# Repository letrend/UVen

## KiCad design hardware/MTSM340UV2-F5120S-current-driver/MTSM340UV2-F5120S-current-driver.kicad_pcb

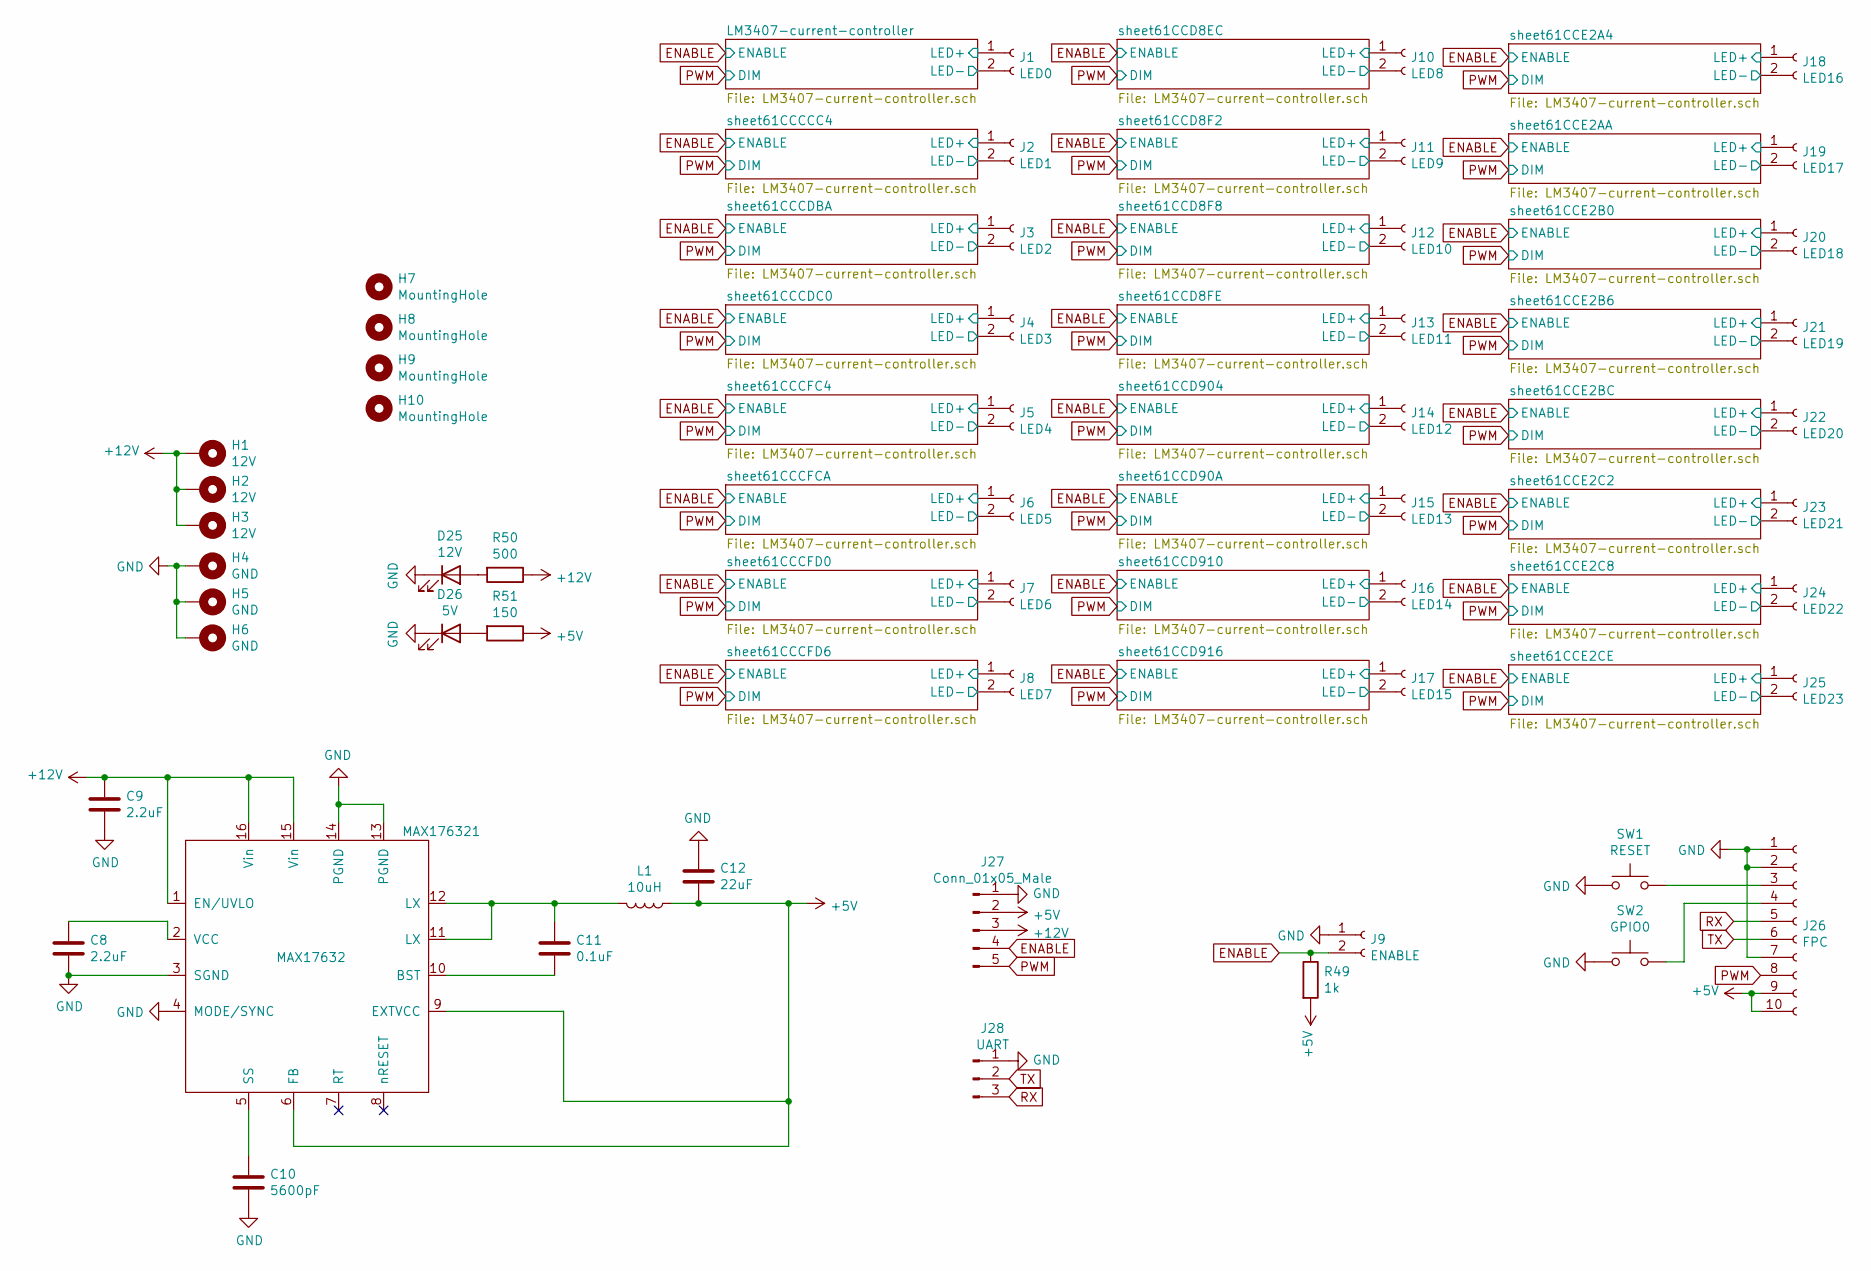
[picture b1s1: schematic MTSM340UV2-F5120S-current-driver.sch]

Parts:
C8, C9: 2.2uF; C_0603_1608Metric_Pad1.08x0.95mm_HandSolder
C10: 5600pF; C_0603_1608Metric_Pad1.08x0.95mm_HandSolder
C11: 0.1uF; C_0805_2012Metric_Pad1.18x1.45mm_HandSolder
C12: 22uF; C_0805_2012Metric_Pad1.18x1.45mm_HandSolder
D25: 12V; LED_0603_1608Metric_Pad1.05x0.95mm_HandSolder
D26: 5V; LED_0603_1608Metric_Pad1.05x0.95mm_HandSolder
H1, H2, H3: 12V; MountingHole_3.2mm_M3_DIN965_Pad_TopBottom
H4, H5, H6: GND; MountingHole_3.2mm_M3_DIN965_Pad_TopBottom
H7, H8, H9, H10: MountingHole; MountingHole_3.2mm_M3_DIN965
J1: LED0; PinHeader_1x02_P2.54mm_Vertical
J2: LED1; PinHeader_1x02_P2.54mm_Vertical
J3: LED2; PinHeader_1x02_P2.54mm_Vertical
J4: LED3; PinHeader_1x02_P2.54mm_Vertical
J5: LED4; PinHeader_1x02_P2.54mm_Vertical
J6: LED5; PinHeader_1x02_P2.54mm_Vertical
J7: LED6; PinHeader_1x02_P2.54mm_Vertical
J8: LED7; PinHeader_1x02_P2.54mm_Vertical
J9: ENABLE; PinHeader_1x02_P2.54mm_Vertical
J10: LED8; PinHeader_1x02_P2.54mm_Vertical
J11: LED9; PinHeader_1x02_P2.54mm_Vertical
J12: LED10; PinHeader_1x02_P2.54mm_Vertical
J13: LED11; PinHeader_1x02_P2.54mm_Vertical
J14: LED12; PinHeader_1x02_P2.54mm_Vertical
J15: LED13; PinHeader_1x02_P2.54mm_Vertical
J16: LED14; PinHeader_1x02_P2.54mm_Vertical
J17: LED15; PinHeader_1x02_P2.54mm_Vertical
J18: LED16; PinHeader_1x02_P2.54mm_Vertical
J19: LED17; PinHeader_1x02_P2.54mm_Vertical
J20: LED18; PinHeader_1x02_P2.54mm_Vertical
J21: LED19; PinHeader_1x02_P2.54mm_Vertical
J22: LED20; PinHeader_1x02_P2.54mm_Vertical
J23: LED21; PinHeader_1x02_P2.54mm_Vertical
J24: LED22; PinHeader_1x02_P2.54mm_Vertical
J25: LED23; PinHeader_1x02_P2.54mm_Vertical
J26: FPC; TE_1-1734839-0_1x10-1MP_P0.5mm_Horizontal
J27: Conn_01x05_Male; PinHeader_1x05_P2.54mm_Vertical
J28: UART; PinHeader_1x03_P2.54mm_Vertical
L1: 10uH; XAL5050-103MEC
MAX176321: MAX17632; QFN-16-1EP_3x3mm_Pitch0.5mm
R49: 1k; R_0603_1608Metric_Pad0.98x0.95mm_HandSolder
R50: 500; R_0603_1608Metric_Pad0.98x0.95mm_HandSolder
R51: 150; R_0603_1608Metric_Pad0.98x0.95mm_HandSolder
SW1: RESET; SW_PUSH_6mm
SW2: GPIO0; SW_PUSH_6mm

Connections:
+5V: C12.2, J26.9, J26.10, J27.2, L1.1, MAX176321.6 (FB), MAX176321.9 (EXTVCC), R49.2, R51.1
+12V: C9.1, H1.1, H2.1, H3.1, J1.1, J2.1, J3.1, J4.1, J5.1, J6.1, J7.1, J8.1, J10.1, J11.1, J12.1, J13.1, J14.1, J15.1, J16.1, J17.1, J18.1, J19.1, J20.1, J21.1, J22.1, J23.1, J24.1, J25.1, J27.3, MAX176321.1 (EN/UVLO), MAX176321.15 (Vin), MAX176321.16 (Vin), R50.1; also elsewhere on the board
/LM3407-current-controller/LED-: J1.2; also elsewhere on the board
/sheet61CCCCC4/LED-: J2.2; also elsewhere on the board
/sheet61CCCDBA/LED-: J3.2; also elsewhere on the board
/sheet61CCCDC0/LED-: J4.2; also elsewhere on the board
/sheet61CCCFC4/LED-: J5.2; also elsewhere on the board
/sheet61CCCFCA/LED-: J6.2; also elsewhere on the board
/sheet61CCCFD0/LED-: J7.2; also elsewhere on the board
/sheet61CCCFD6/LED-: J8.2; also elsewhere on the board
/sheet61CCD8EC/LED-: J10.2; also elsewhere on the board
/sheet61CCD8F2/LED-: J11.2; also elsewhere on the board
/sheet61CCD8F8/LED-: J12.2; also elsewhere on the board
/sheet61CCD8FE/LED-: J13.2; also elsewhere on the board
/sheet61CCD90A/LED-: J15.2; also elsewhere on the board
/sheet61CCD904/LED-: J14.2; also elsewhere on the board
/sheet61CCD910/LED-: J16.2; also elsewhere on the board
/sheet61CCD916/LED-: J17.2; also elsewhere on the board
/sheet61CCE2A4/LED-: J18.2; also elsewhere on the board
/sheet61CCE2AA/LED-: J19.2; also elsewhere on the board
/sheet61CCE2B0/LED-: J20.2; also elsewhere on the board
/sheet61CCE2B6/LED-: J21.2; also elsewhere on the board
/sheet61CCE2BC/LED-: J22.2; also elsewhere on the board
/sheet61CCE2C2/LED-: J23.2; also elsewhere on the board
/sheet61CCE2C8/LED-: J24.2; also elsewhere on the board
/sheet61CCE2CE/LED-: J25.2; also elsewhere on the board
ENABLE: J9.2, J27.4, R49.1; also elsewhere on the board
GND: C8.2, C9.2, C10.2, C12.1, D25.1 (K), D26.1 (K), H4.1, H5.1, H6.1, J9.1, J26.1, J26.2, J26.7, J27.1, J28.1, MAX176321.3 (SGND), MAX176321.4 (MODE/SYNC), MAX176321.13 (PGND), MAX176321.14 (PGND), SW1.1, SW2.1; also elsewhere on the board
unnamed: C8.1, MAX176321.2 (VCC)
unnamed: C10.1, MAX176321.5 (SS)
unnamed: C11.1, L1.2, MAX176321.11 (LX), MAX176321.12 (LX)
unnamed: C11.2, MAX176321.10 (BST)
unnamed: D25.2 (A), R50.2
unnamed: D26.2 (A), R51.2
unnamed: J26.3, SW1.2
unnamed: J26.4, SW2.2
PWM: J26.8, J27.5; also elsewhere on the board
RX: J26.5, J28.3
TX: J26.6, J28.2

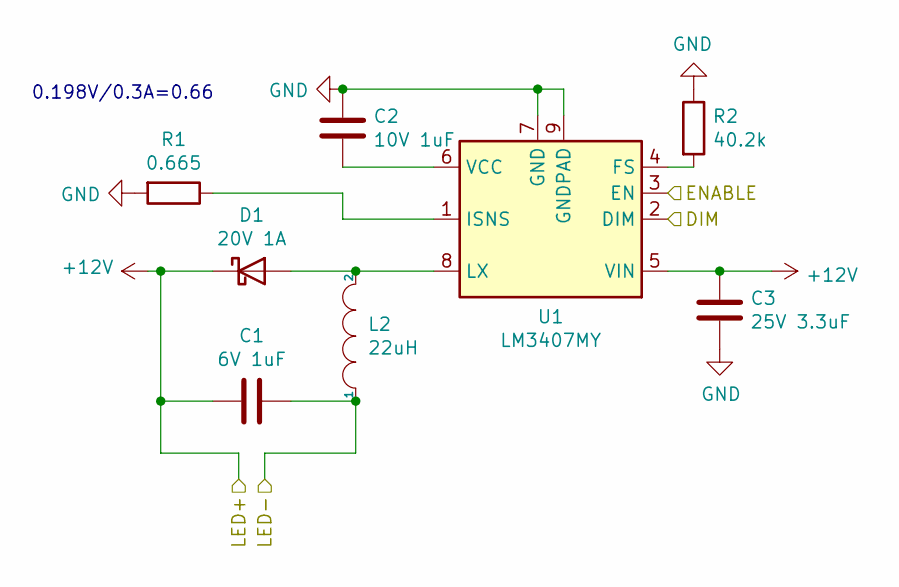
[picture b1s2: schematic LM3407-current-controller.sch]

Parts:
C1: 6V 1uF; C_0603_1608Metric_Pad1.08x0.95mm_HandSolder
C2: 10V 1uF; C_0603_1608Metric_Pad1.08x0.95mm_HandSolder
C3: 25V 3.3uF; C_0603_1608Metric_Pad1.08x0.95mm_HandSolder
D1: 20V 1A; D_PowerDI-123
L2: 22uH; LQH3NPN
R1: 0.665; R_1206_3216Metric_Pad1.30x1.75mm_HandSolder
R2: 40.2k; R_0603_1608Metric_Pad0.98x0.95mm_HandSolder
U1: LM3407MY; MSOP-8-1EP_3x3mm_P0.65mm_EP1.73x1.85mm_ThermalVias

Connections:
+12V: C1.2, C3.1, D1.1 (K), U1.5 (VIN); also elsewhere on the board
/LM3407-current-controller/LED-: C1.1, L2.1; also elsewhere on the board
ENABLE: U1.3 (EN); also elsewhere on the board
GND: C2.1, C3.2, R1.2, R2.1, U1.7 (GND), U1.9 (GNDPAD); also elsewhere on the board
unnamed: C2.2, U1.6 (VCC)
unnamed: D1.2 (A), L2.2, U1.8 (LX)
unnamed: R1.1, U1.1 (ISNS)
unnamed: R2.2, U1.4 (FS)
PWM: U1.2 (DIM); also elsewhere on the board

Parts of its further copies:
C4, C7, C15, C18, C21, C24, C27, C30, C33, C36, C39, C42, C45, C48, C51, C54, C57, C60, C63, C66, C69, C72, C75: 6V 1uF; C_0603_1608Metric_Pad1.08x0.95mm_HandSolder
C5, C13, C16, C19, C22, C25, C28, C31, C34, C37, C40, C43, C46, C49, C52, C55, C58, C61, C64, C67, C70, C73, C76: 10V 1uF; C_0603_1608Metric_Pad1.08x0.95mm_HandSolder
C6, C14, C17, C20, C23, C26, C29, C32, C35, C38, C41, C44, C47, C50, C53, C56, C59, C62, C65, C68, C71, C74, C77: 25V 3.3uF; C_0603_1608Metric_Pad1.08x0.95mm_HandSolder
D2, D3, D4, D5, D6, D7, D8, D9, D10, D11, D12, D13, D14, D15, D16, D17, D18, D19, D20, D21, D22, D23, D24: 20V 1A; D_PowerDI-123
L3, L4, L5, L6, L7, L8, L9, L10, L11, L12, L13, L14, L15, L16, L17, L18, L19, L20, L21, L22, L23, L24, L25: 22uH; LQH3NPN
R3, R5, R7, R9, R11, R13, R15, R17, R19, R21, R23, R25, R27, R29, R31, R33, R35, R37, R39, R41, R43, R45, R47: 0.665; R_1206_3216Metric_Pad1.30x1.75mm_HandSolder
R4, R6, R8, R10, R12, R14, R16, R18, R20, R22, R24, R26, R28, R30, R32, R34, R36, R38, R40, R42, R44, R46, R48: 40.2k; R_0603_1608Metric_Pad0.98x0.95mm_HandSolder
U2, U3, U4, U5, U6, U7, U8, U9, U10, U11, U12, U13, U14, U15, U16, U17, U18, U19, U20, U21, U22, U23, U24: LM3407MY; MSOP-8-1EP_3x3mm_P0.65mm_EP1.73x1.85mm_ThermalVias

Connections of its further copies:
+12V: C4.2, C6.1, C7.2, C14.1, C15.2, C17.1, C18.2, C20.1, C21.2, C23.1, C24.2, C26.1, C27.2, C29.1, C30.2, C32.1, C33.2, C35.1, C36.2, C38.1, C39.2, C41.1, C42.2, C44.1, C45.2, C47.1, C48.2, C50.1, C51.2, C53.1, C54.2, C56.1, C57.2, C59.1, C60.2, C62.1, C63.2, C65.1, C66.2, C68.1, C69.2, C71.1, C72.2, C74.1, C75.2, C77.1, D2.1 (K), D3.1 (K), D4.1 (K), D5.1 (K), D6.1 (K), D7.1 (K), D8.1 (K), D9.1 (K), D10.1 (K), D11.1 (K), D12.1 (K), D13.1 (K), D14.1 (K), D15.1 (K), D16.1 (K), D17.1 (K), D18.1 (K), D19.1 (K), D20.1 (K), D21.1 (K), D22.1 (K), D23.1 (K), D24.1 (K), U2.5 (VIN), U3.5 (VIN), U4.5 (VIN), U5.5 (VIN), U6.5 (VIN), U7.5 (VIN), U8.5 (VIN), U9.5 (VIN), U10.5 (VIN), U11.5 (VIN), U12.5 (VIN), U13.5 (VIN), U14.5 (VIN), U15.5 (VIN), U16.5 (VIN), U17.5 (VIN), U18.5 (VIN), U19.5 (VIN), U20.5 (VIN), U21.5 (VIN), U22.5 (VIN), U23.5 (VIN), U24.5 (VIN); also elsewhere on the board
/sheet61CCCCC4/LED-: C4.1, L3.1; also elsewhere on the board
/sheet61CCCDBA/LED-: C7.1, L4.1; also elsewhere on the board
/sheet61CCCDC0/LED-: C15.1, L5.1; also elsewhere on the board
/sheet61CCCFC4/LED-: C18.1, L6.1; also elsewhere on the board
/sheet61CCCFCA/LED-: C21.1, L7.1; also elsewhere on the board
/sheet61CCCFD0/LED-: C24.1, L8.1; also elsewhere on the board
/sheet61CCCFD6/LED-: C27.1, L9.1; also elsewhere on the board
/sheet61CCD8EC/LED-: C30.1, L10.1; also elsewhere on the board
/sheet61CCD8F2/LED-: C33.1, L11.1; also elsewhere on the board
/sheet61CCD8F8/LED-: C36.1, L12.1; also elsewhere on the board
/sheet61CCD8FE/LED-: C39.1, L13.1; also elsewhere on the board
/sheet61CCD90A/LED-: C45.1, L15.1; also elsewhere on the board
/sheet61CCD904/LED-: C42.1, L14.1; also elsewhere on the board
/sheet61CCD910/LED-: C48.1, L16.1; also elsewhere on the board
/sheet61CCD916/LED-: C51.1, L17.1; also elsewhere on the board
/sheet61CCE2A4/LED-: C54.1, L18.1; also elsewhere on the board
/sheet61CCE2AA/LED-: C57.1, L19.1; also elsewhere on the board
/sheet61CCE2B0/LED-: C60.1, L20.1; also elsewhere on the board
/sheet61CCE2B6/LED-: C63.1, L21.1; also elsewhere on the board
/sheet61CCE2BC/LED-: C66.1, L22.1; also elsewhere on the board
/sheet61CCE2C2/LED-: C69.1, L23.1; also elsewhere on the board
/sheet61CCE2C8/LED-: C72.1, L24.1; also elsewhere on the board
/sheet61CCE2CE/LED-: C75.1, L25.1; also elsewhere on the board
ENABLE: U2.3 (EN), U3.3 (EN), U4.3 (EN), U5.3 (EN), U6.3 (EN), U7.3 (EN), U8.3 (EN), U9.3 (EN), U10.3 (EN), U11.3 (EN), U12.3 (EN), U13.3 (EN), U14.3 (EN), U15.3 (EN), U16.3 (EN), U17.3 (EN), U18.3 (EN), U19.3 (EN), U20.3 (EN), U21.3 (EN), U22.3 (EN), U23.3 (EN), U24.3 (EN); also elsewhere on the board
GND: C5.1, C6.2, C13.1, C14.2, C16.1, C17.2, C19.1, C20.2, C22.1, C23.2, C25.1, C26.2, C28.1, C29.2, C31.1, C32.2, C34.1, C35.2, C37.1, C38.2, C40.1, C41.2, C43.1, C44.2, C46.1, C47.2, C49.1, C50.2, C52.1, C53.2, C55.1, C56.2, C58.1, C59.2, C61.1, C62.2, C64.1, C65.2, C67.1, C68.2, C70.1, C71.2, C73.1, C74.2, C76.1, C77.2, R3.2, R4.1, R5.2, R6.1, R7.2, R8.1, R9.2, R10.1, R11.2, R12.1, R13.2, R14.1, R15.2, R16.1, R17.2, R18.1, R19.2, R20.1, R21.2, R22.1, R23.2, R24.1, R25.2, R26.1, R27.2, R28.1, R29.2, R30.1, R31.2, R32.1, R33.2, R34.1, R35.2, R36.1, R37.2, R38.1, R39.2, R40.1, R41.2, R42.1, R43.2, R44.1, R45.2, R46.1, R47.2, R48.1, U2.7 (GND), U2.9 (GNDPAD), U3.7 (GND), U3.9 (GNDPAD), U4.7 (GND), U4.9 (GNDPAD), U5.7 (GND), U5.9 (GNDPAD), U6.7 (GND), U6.9 (GNDPAD), U7.7 (GND), U7.9 (GNDPAD), U8.7 (GND), U8.9 (GNDPAD), U9.7 (GND), U9.9 (GNDPAD), U10.7 (GND), U10.9 (GNDPAD), U11.7 (GND), U11.9 (GNDPAD), U12.7 (GND), U12.9 (GNDPAD), U13.7 (GND), U13.9 (GNDPAD), U14.7 (GND), U14.9 (GNDPAD), U15.7 (GND), U15.9 (GNDPAD), U16.7 (GND), U16.9 (GNDPAD), U17.7 (GND), U17.9 (GNDPAD), U18.7 (GND), U18.9 (GNDPAD), U19.7 (GND), U19.9 (GNDPAD), U20.7 (GND), U20.9 (GNDPAD), U21.7 (GND), U21.9 (GNDPAD), U22.7 (GND), U22.9 (GNDPAD), U23.7 (GND), U23.9 (GNDPAD), U24.7 (GND), U24.9 (GNDPAD); also elsewhere on the board
unnamed: C5.2, U2.6 (VCC)
unnamed: C13.2, U3.6 (VCC)
unnamed: C16.2, U4.6 (VCC)
unnamed: C19.2, U5.6 (VCC)
unnamed: C22.2, U6.6 (VCC)
unnamed: C25.2, U7.6 (VCC)
unnamed: C28.2, U8.6 (VCC)
unnamed: C31.2, U9.6 (VCC)
unnamed: C34.2, U10.6 (VCC)
unnamed: C37.2, U11.6 (VCC)
unnamed: C40.2, U12.6 (VCC)
unnamed: C43.2, U13.6 (VCC)
unnamed: C46.2, U14.6 (VCC)
unnamed: C49.2, U15.6 (VCC)
unnamed: C52.2, U16.6 (VCC)
unnamed: C55.2, U17.6 (VCC)
unnamed: C58.2, U18.6 (VCC)
unnamed: C61.2, U19.6 (VCC)
unnamed: C64.2, U20.6 (VCC)
unnamed: C67.2, U21.6 (VCC)
unnamed: C70.2, U22.6 (VCC)
unnamed: C73.2, U23.6 (VCC)
unnamed: C76.2, U24.6 (VCC)
unnamed: D2.2 (A), L3.2, U2.8 (LX)
unnamed: D3.2 (A), L4.2, U3.8 (LX)
unnamed: D4.2 (A), L5.2, U4.8 (LX)
unnamed: D5.2 (A), L6.2, U5.8 (LX)
unnamed: D6.2 (A), L7.2, U6.8 (LX)
unnamed: D7.2 (A), L8.2, U7.8 (LX)
unnamed: D8.2 (A), L9.2, U8.8 (LX)
unnamed: D9.2 (A), L10.2, U9.8 (LX)
unnamed: D10.2 (A), L11.2, U10.8 (LX)
unnamed: D11.2 (A), L12.2, U11.8 (LX)
unnamed: D12.2 (A), L13.2, U12.8 (LX)
unnamed: D13.2 (A), L14.2, U13.8 (LX)
unnamed: D14.2 (A), L15.2, U14.8 (LX)
unnamed: D15.2 (A), L16.2, U15.8 (LX)
unnamed: D16.2 (A), L17.2, U16.8 (LX)
unnamed: D17.2 (A), L18.2, U17.8 (LX)
unnamed: D18.2 (A), L19.2, U18.8 (LX)
unnamed: D19.2 (A), L20.2, U19.8 (LX)
unnamed: D20.2 (A), L21.2, U20.8 (LX)
unnamed: D21.2 (A), L22.2, U21.8 (LX)
unnamed: D22.2 (A), L23.2, U22.8 (LX)
unnamed: D23.2 (A), L24.2, U23.8 (LX)
unnamed: D24.2 (A), L25.2, U24.8 (LX)
unnamed: R3.1, U2.1 (ISNS)
unnamed: R4.2, U2.4 (FS)
unnamed: R5.1, U3.1 (ISNS)
unnamed: R6.2, U3.4 (FS)
unnamed: R7.1, U4.1 (ISNS)
unnamed: R8.2, U4.4 (FS)
unnamed: R9.1, U5.1 (ISNS)
unnamed: R10.2, U5.4 (FS)
unnamed: R11.1, U6.1 (ISNS)
unnamed: R12.2, U6.4 (FS)
unnamed: R13.1, U7.1 (ISNS)
unnamed: R14.2, U7.4 (FS)
unnamed: R15.1, U8.1 (ISNS)
unnamed: R16.2, U8.4 (FS)
unnamed: R17.1, U9.1 (ISNS)
unnamed: R18.2, U9.4 (FS)
unnamed: R19.1, U10.1 (ISNS)
unnamed: R20.2, U10.4 (FS)
unnamed: R21.1, U11.1 (ISNS)
unnamed: R22.2, U11.4 (FS)
unnamed: R23.1, U12.1 (ISNS)
unnamed: R24.2, U12.4 (FS)
unnamed: R25.1, U13.1 (ISNS)
unnamed: R26.2, U13.4 (FS)
unnamed: R27.1, U14.1 (ISNS)
unnamed: R28.2, U14.4 (FS)
unnamed: R29.1, U15.1 (ISNS)
unnamed: R30.2, U15.4 (FS)
unnamed: R31.1, U16.1 (ISNS)
unnamed: R32.2, U16.4 (FS)
unnamed: R33.1, U17.1 (ISNS)
unnamed: R34.2, U17.4 (FS)
unnamed: R35.1, U18.1 (ISNS)
unnamed: R36.2, U18.4 (FS)
unnamed: R37.1, U19.1 (ISNS)
unnamed: R38.2, U19.4 (FS)
unnamed: R39.1, U20.1 (ISNS)
unnamed: R40.2, U20.4 (FS)
unnamed: R41.1, U21.1 (ISNS)
unnamed: R42.2, U21.4 (FS)
unnamed: R43.1, U22.1 (ISNS)
unnamed: R44.2, U22.4 (FS)
unnamed: R45.1, U23.1 (ISNS)
unnamed: R46.2, U23.4 (FS)
unnamed: R47.1, U24.1 (ISNS)
unnamed: R48.2, U24.4 (FS)
PWM: U2.2 (DIM), U3.2 (DIM), U4.2 (DIM), U5.2 (DIM), U6.2 (DIM), U7.2 (DIM), U8.2 (DIM), U9.2 (DIM), U10.2 (DIM), U11.2 (DIM), U12.2 (DIM), U13.2 (DIM), U14.2 (DIM), U15.2 (DIM), U16.2 (DIM), U17.2 (DIM), U18.2 (DIM), U19.2 (DIM), U20.2 (DIM), U21.2 (DIM), U22.2 (DIM), U23.2 (DIM), U24.2 (DIM); also elsewhere on the board

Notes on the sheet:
0.198V/0.3A=0.66

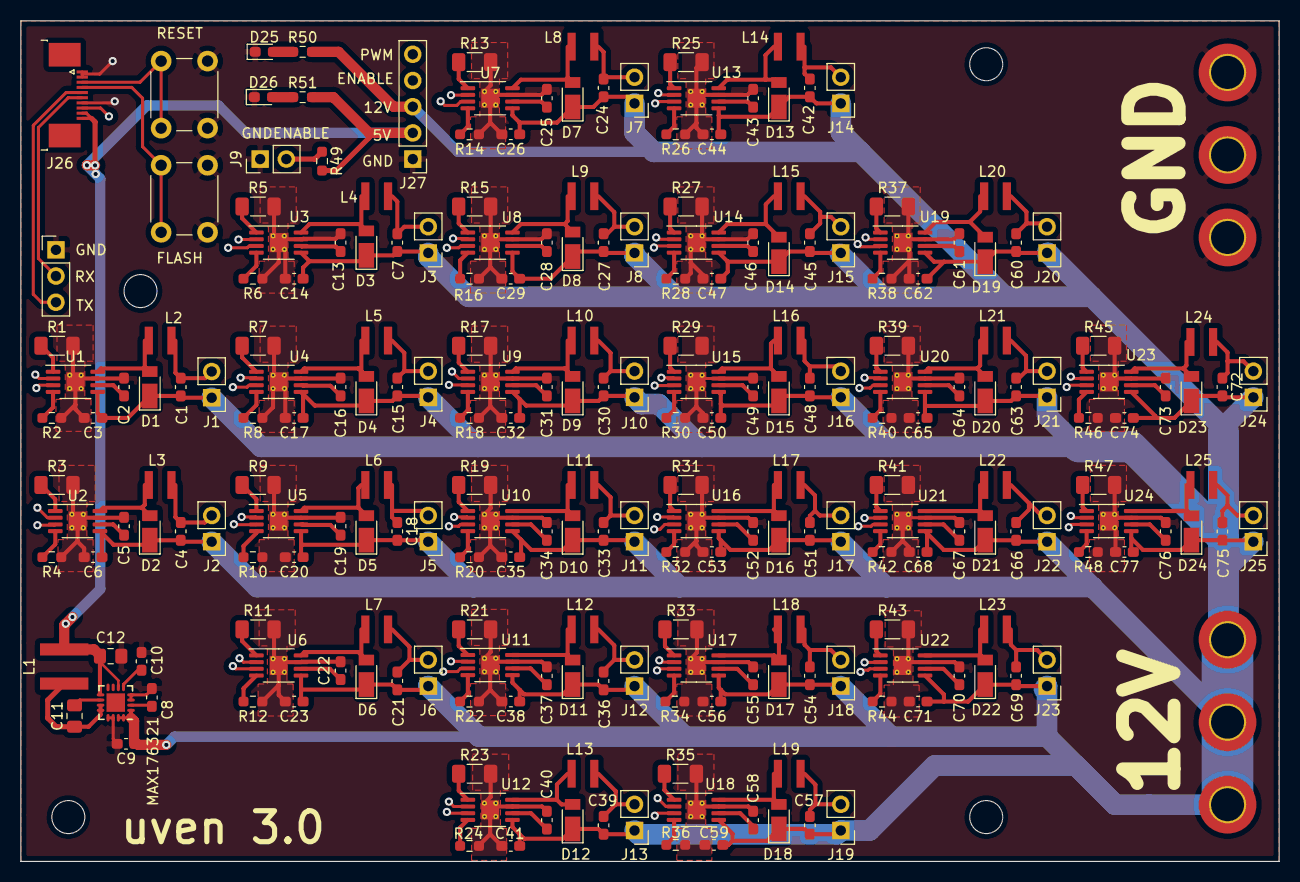
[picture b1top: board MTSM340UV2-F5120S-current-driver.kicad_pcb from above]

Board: 4 copper layers, 122.0 x 81.5 mm, 244 parts (0 on the bottom side), 135 nets.

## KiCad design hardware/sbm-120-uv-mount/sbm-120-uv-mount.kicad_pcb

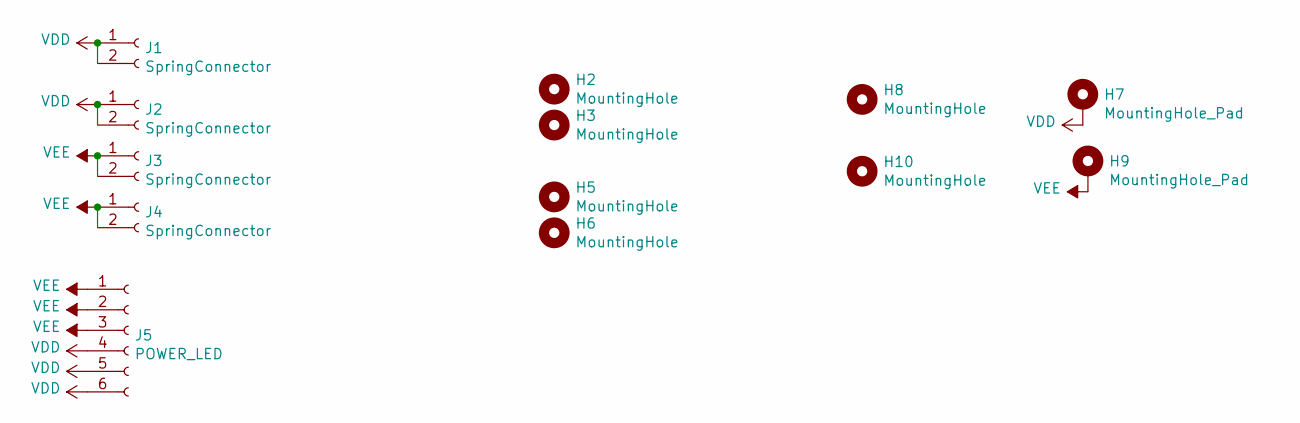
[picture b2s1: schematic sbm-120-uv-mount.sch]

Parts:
H2, H3, H5, H6: MountingHole; MountingHole_3.2mm_M3
H7, H9: MountingHole_Pad; MountingHole_2.2mm_M2_DIN965_Pad
H8, H10: MountingHole; MountingHole_2.2mm_M2
J1, J2, J3, J4: SpringConnector; 22862113
J5: POWER_LED; PinHeader_1x06_P2.54mm_Vertical

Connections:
VDD: H7.1, J1.1, J1.2, J2.1, J2.2, J5.4, J5.5, J5.6
VEE: H9.1, J3.1, J3.2, J4.1, J4.2, J5.1, J5.2, J5.3

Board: 2 copper layers, 13 parts (1 on the bottom side), 2 nets, no tracks yet.

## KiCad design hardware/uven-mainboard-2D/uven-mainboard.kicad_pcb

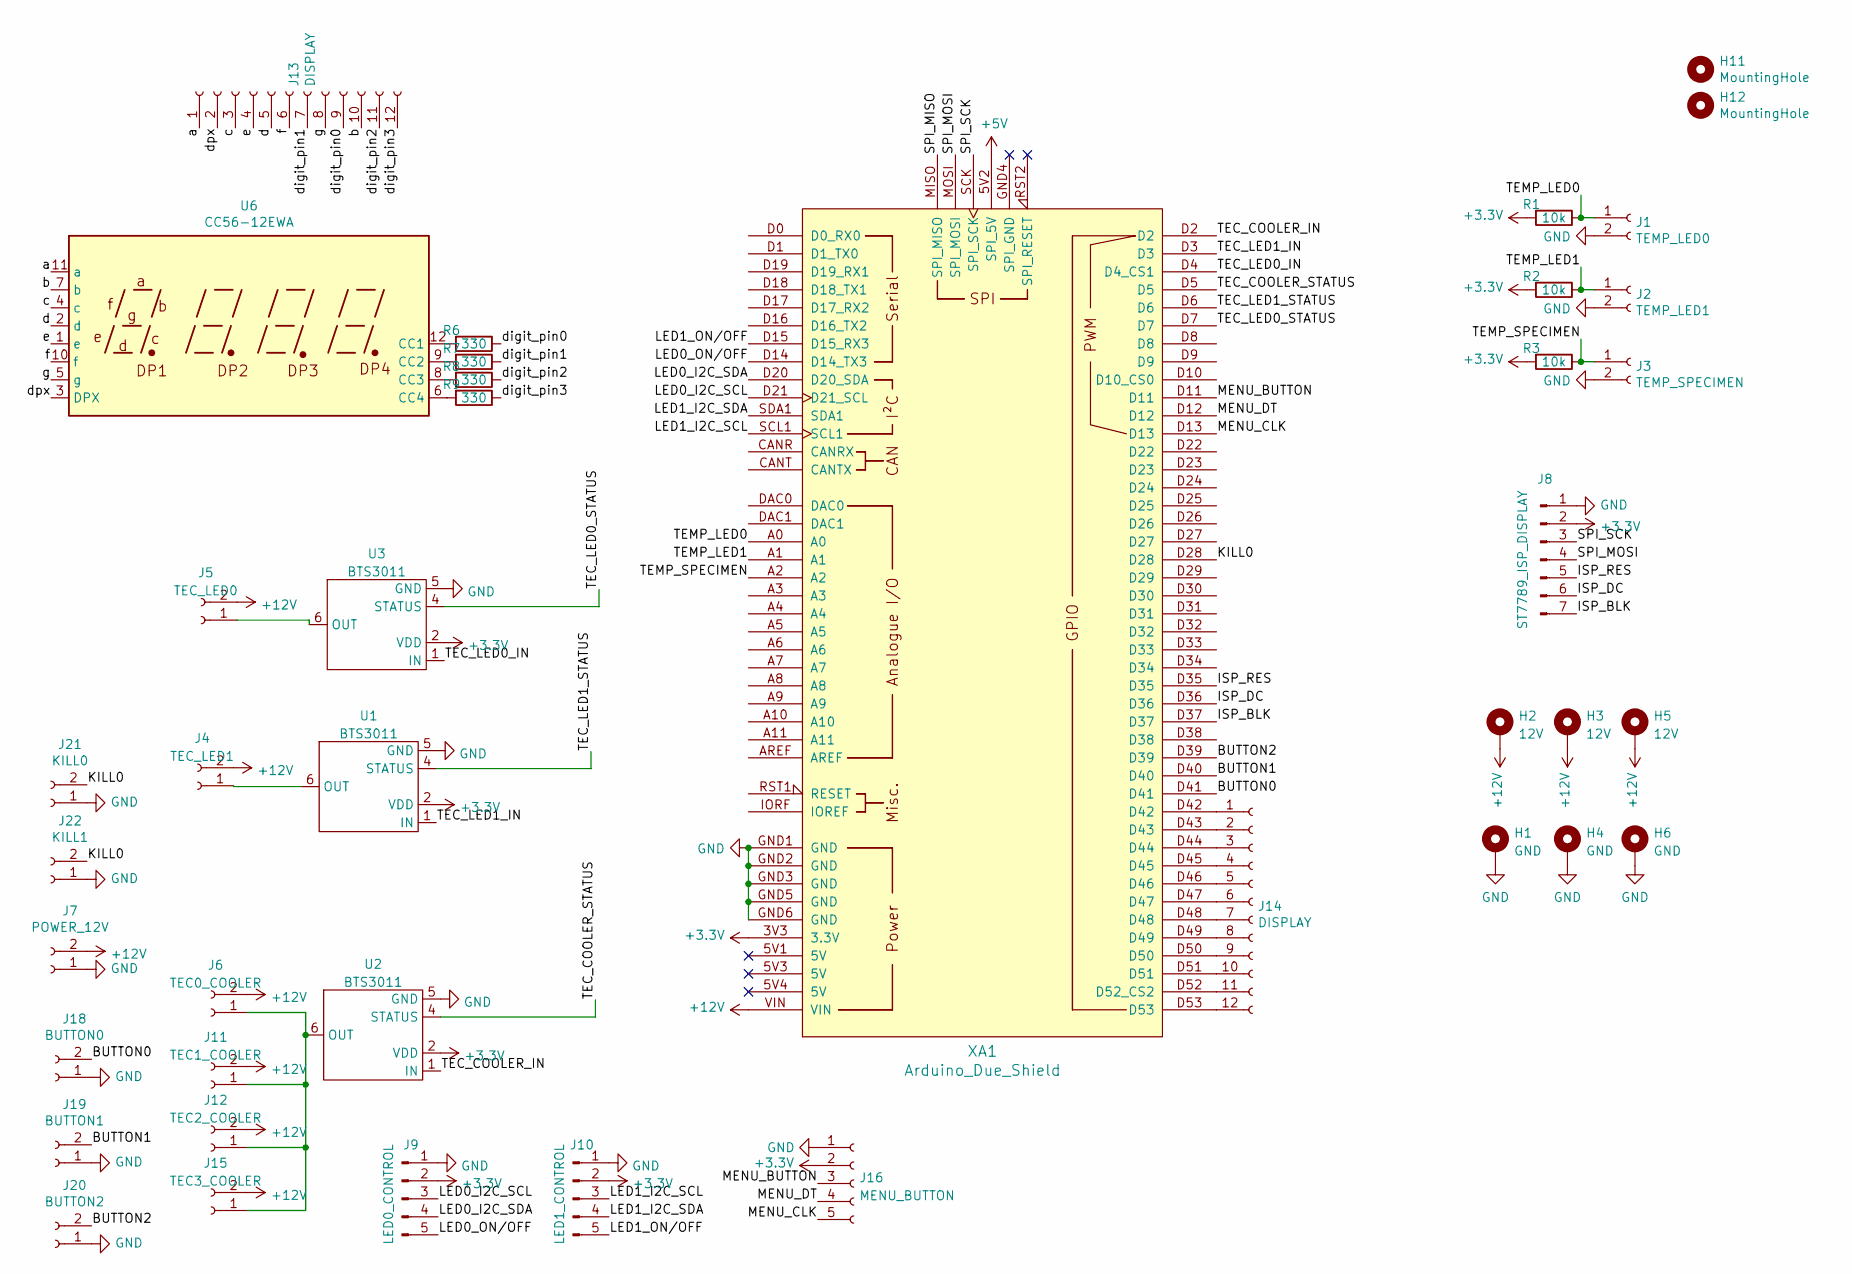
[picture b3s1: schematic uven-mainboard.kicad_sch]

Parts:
H1, H4, H6: GND; MountingHole_3.2mm_M3_DIN965_Pad_TopBottom
H2, H3, H5: 12V; MountingHole_3.2mm_M3_DIN965_Pad_TopBottom
H11, H12: MountingHole; MountingHole_3.2mm_M3
J1: TEMP_LED0; PinSocket_1x02_P2.54mm_Vertical
J2: TEMP_LED1; PinSocket_1x02_P2.54mm_Vertical
J3: TEMP_SPECIMEN; PinSocket_1x02_P2.54mm_Vertical
J4: TEC_LED1; PinHeader_1x02_P2.54mm_Vertical
J5: TEC_LED0; PinHeader_1x02_P2.54mm_Vertical
J6: TEC0_COOLER; PinHeader_1x02_P2.54mm_Vertical
J7: POWER_12V; PinSocket_1x02_P2.54mm_Vertical
J8: ST7789_ISP_DISPLAY; PinHeader_1x07_P2.54mm_Vertical
J9: LED0_CONTROL; PinHeader_1x05_P2.54mm_Vertical
J10: LED1_CONTROL; PinHeader_1x05_P2.54mm_Vertical
J11: TEC1_COOLER; PinHeader_1x02_P2.54mm_Vertical
J12: TEC2_COOLER; PinHeader_1x02_P2.54mm_Vertical
J13, J14: DISPLAY; PinHeader_1x12_P2.54mm_Vertical
J15: TEC3_COOLER; PinHeader_1x02_P2.54mm_Vertical
J16: MENU_BUTTON; PinHeader_1x05_P2.54mm_Vertical
J18: BUTTON0; PinSocket_1x02_P2.54mm_Vertical
J19: BUTTON1; PinSocket_1x02_P2.54mm_Vertical
J20: BUTTON2; PinSocket_1x02_P2.54mm_Vertical
J21: KILL0; PinSocket_1x02_P2.54mm_Vertical
J22: KILL1; PinSocket_1x02_P2.54mm_Vertical
R1, R2, R3: 10k; R_0603_1608Metric_Pad1.05x0.95mm_HandSolder
R6, R7, R8, R9: 330; R_0603_1608Metric_Pad1.05x0.95mm_HandSolder
U1, U2, U3: BTS3011
U6: CC56-12EWA; 3461AS-1
XA1: Arduino_Due_Shield

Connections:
+3V3: J8.2, J9.2, J10.2, J16.2, R1.2, R2.2, R3.2, U1.2 (VDD), U2.2 (VDD), U3.2 (VDD), XA1.3V3 (3.3V)
+5V: XA1.5V2 (SPI_5V)
+12V: H2.1, H3.1, H5.1, J4.2, J5.2, J6.2, J7.2, J11.2, J12.2, J15.2, XA1.VIN
/BUTTON0: J18.2, XA1.D41
/BUTTON1: J19.2, XA1.D40
/BUTTON2: J20.2, XA1.D39
/ISP_BLK: J8.7, XA1.D37
/ISP_DC: J8.6, XA1.D36
/ISP_RES: J8.5, XA1.D35
/KILL0: J21.2, J22.2, XA1.D28
/LED0_I2C_SCL: J9.3, XA1.D21 (D21_SCL)
/LED0_I2C_SDA: J9.4, XA1.D20 (D20_SDA)
/LED0_ON/OFF: J9.5, XA1.D14 (D14_TX3)
/LED1_I2C_SCL: J10.3, XA1.SCL1
/LED1_I2C_SDA: J10.4, XA1.SDA1
/LED1_ON/OFF: J10.5, XA1.D15 (D15_RX3)
/MENU_BUTTON: J16.3, XA1.D11
/MENU_CLK: J16.5, XA1.D13
/MENU_DT: J16.4, XA1.D12
/SPI_MISO: XA1.MISO (SPI_MISO)
/SPI_MOSI: J8.4, XA1.MOSI (SPI_MOSI)
/SPI_SCK: J8.3, XA1.SCK (SPI_SCK)
/TEC_COOLER_IN: U2.1 (IN), XA1.D2
/TEC_COOLER_STATUS: U2.4 (STATUS), XA1.D5
/TEC_LED0_IN: U3.1 (IN), XA1.D4 (D4_CS1)
/TEC_LED0_STATUS: U3.4 (STATUS), XA1.D7
/TEC_LED1_IN: U1.1 (IN), XA1.D3
/TEC_LED1_STATUS: U1.4 (STATUS), XA1.D6
/TEMP_LED0: J1.1, R1.1, XA1.A0
/TEMP_LED1: J2.1, R2.1, XA1.A1
/TEMP_SPECIMEN: J3.1, R3.1, XA1.A2
/a: J13.1, U6.11 (a)
/b: J13.10, U6.7 (b)
/c: J13.3, U6.4 (c)
/d: J13.5, U6.2 (d)
/digit_pin0: J13.9, R6.1
/digit_pin1: J13.7, R7.1
/digit_pin2: J13.11, R8.1
/digit_pin3: J13.12, R9.1
/dpx: J13.2, U6.3 (DPX)
/e: J13.4, U6.1 (e)
/f: J13.6, U6.10 (f)
/g: J13.8, U6.5 (g)
GND: H1.1, H4.1, H6.1, J1.2, J2.2, J3.2, J7.1, J8.1, J9.1, J10.1, J16.1, J18.1, J19.1, J20.1, J21.1, J22.1, U1.5 (GND), U2.5 (GND), U3.5 (GND), XA1.GND1 (GND), XA1.GND2 (GND), XA1.GND3 (GND), XA1.GND5 (GND), XA1.GND6 (GND)
unnamed: J6.1, J11.1, J12.1, J15.1, U2.6 (OUT)
unnamed: R6.2, U6.12 (CC1)
unnamed: R7.2, U6.9 (CC2)
unnamed: R8.2, U6.8 (CC3)
unnamed: R9.2, U6.6 (CC4)
unnamed: J4.1, U1.6 (OUT)
unnamed: J5.1, U3.6 (OUT)
unnamed: J14.1, XA1.D42
unnamed: J14.2, XA1.D43
unnamed: J14.3, XA1.D44
unnamed: J14.4, XA1.D45
unnamed: J14.5, XA1.D46
unnamed: J14.6, XA1.D47
unnamed: J14.7, XA1.D48
unnamed: J14.8, XA1.D49
unnamed: J14.9, XA1.D50
unnamed: J14.10, XA1.D51
unnamed: J14.11, XA1.D52 (D52_CS2)
unnamed: J14.12, XA1.D53

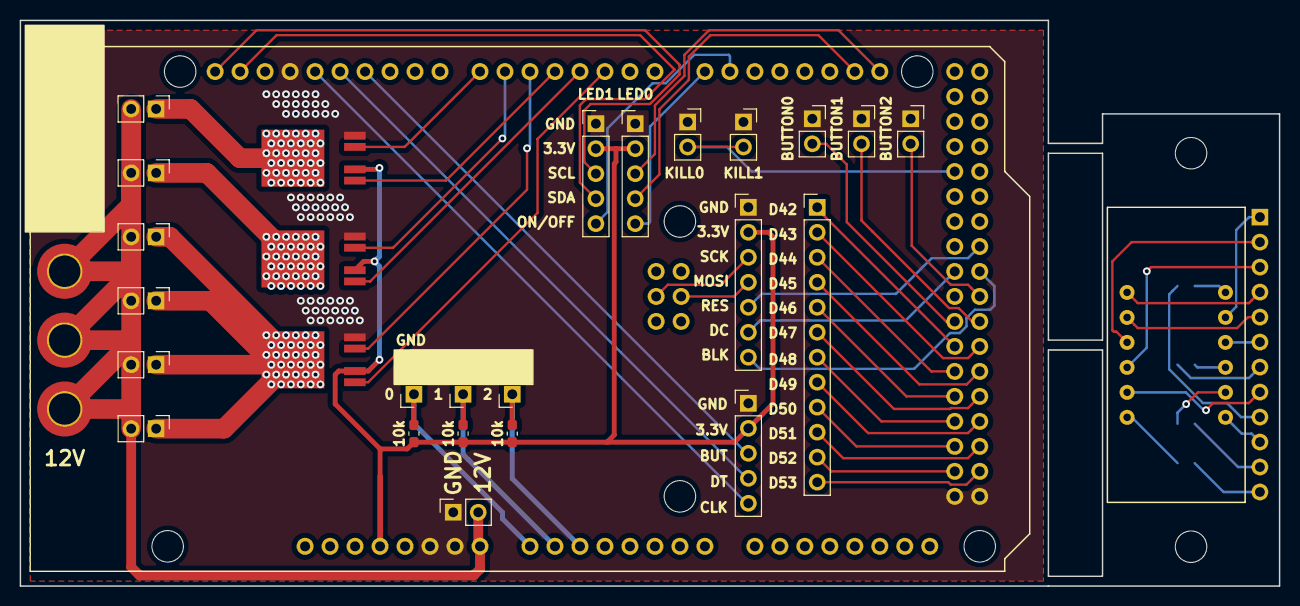
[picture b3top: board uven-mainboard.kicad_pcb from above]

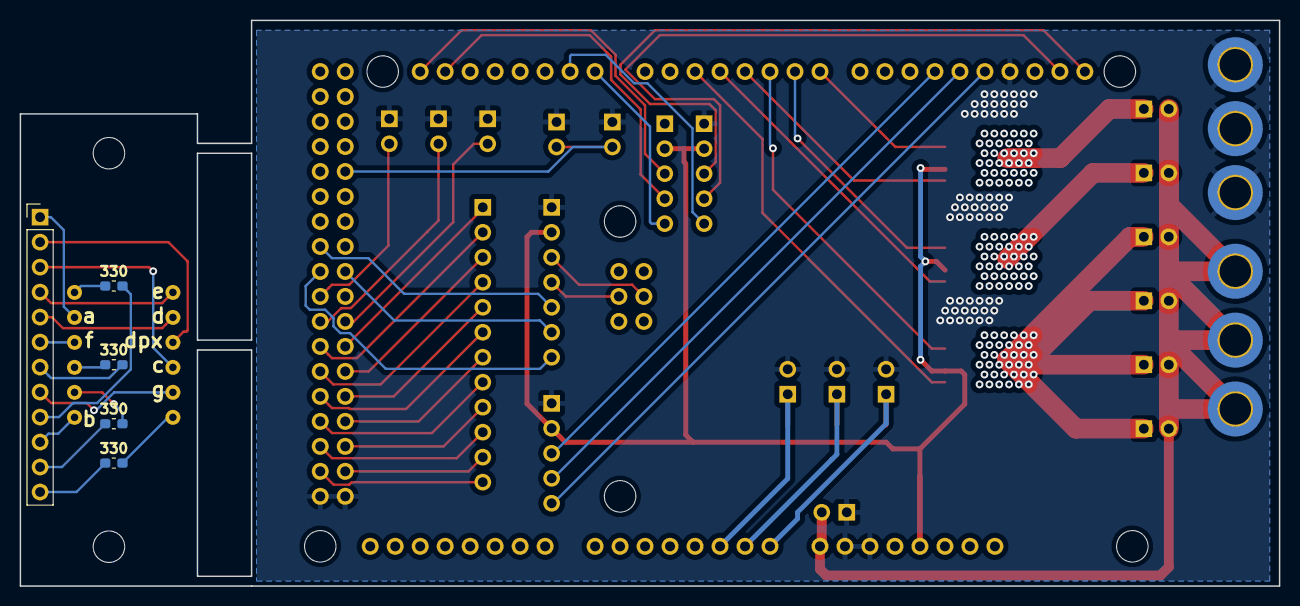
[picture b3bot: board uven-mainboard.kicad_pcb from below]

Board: 2 copper layers, 128.0 x 57.5 mm, 41 parts (5 on the bottom side), 61 nets.
